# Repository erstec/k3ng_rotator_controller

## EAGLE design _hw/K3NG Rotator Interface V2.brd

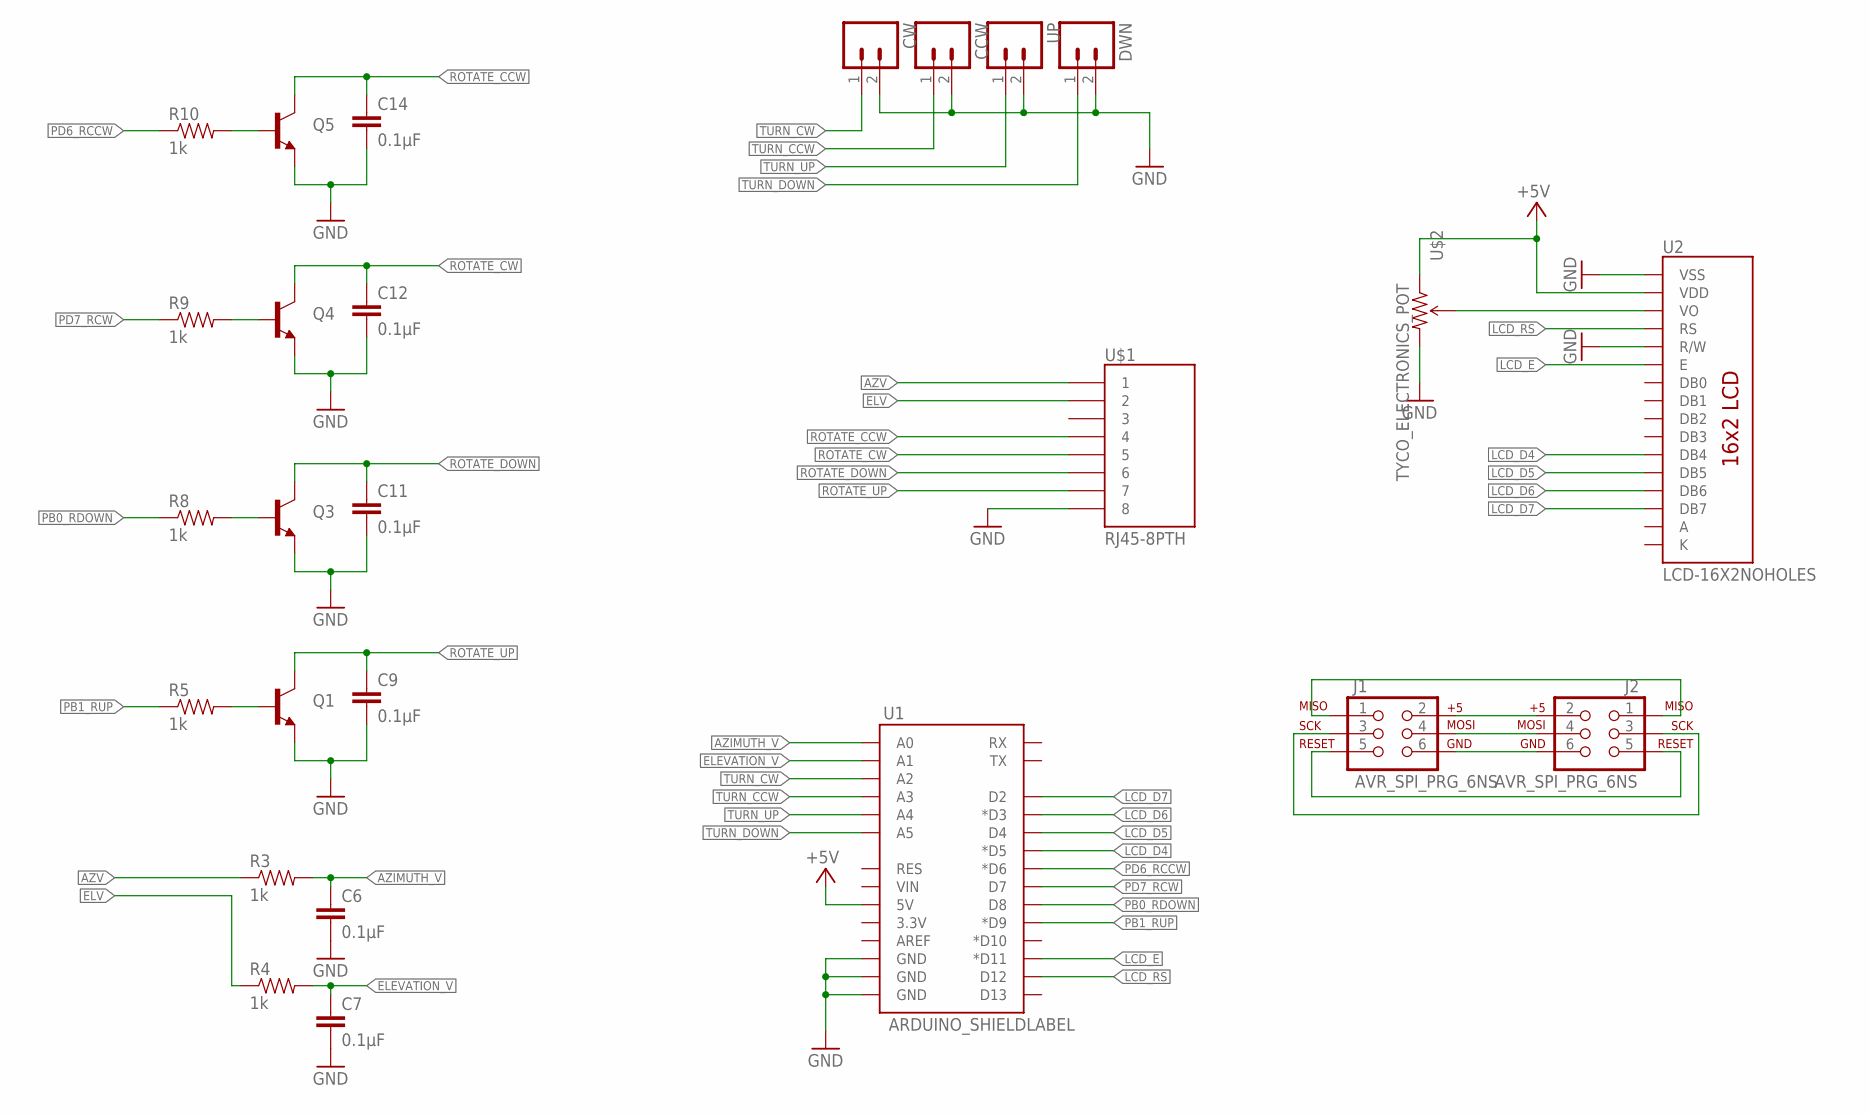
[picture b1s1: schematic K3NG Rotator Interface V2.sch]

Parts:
C6, C7, C9, C11, C12, C14: 0.1µF; 0603-CAP
CCW: M02PTH; 1X02
CW: M02PTH; 1X02
DWN: M02PTH; 1X02
J1, J2: AVR_SPI_PRG_6NS; 2X3-NS
Q1, Q3, Q4, Q5: TRANSISTOR_NPNSOT23; SOT23
R3, R4, R5, R8, R9, R10: 1k; 0805
U1: ARDUINO_SHIELDLABEL; DUEMILANOVE_SHIELD
U2: LCD-16X2NOHOLES; LCD-16X2_NOHOLES
U$1: RJ45-8PTH; RJ45-8
U$2: TYCO_ELECTRONICS_POT
UP: M02PTH; 1X02

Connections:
+5V: U1.5V, U2.2 (VDD), U$2.P$1 (CCW)
A: U2.15 (A)
AZIMUTH_V: C6.1, R3.2, U1.A0
AZV: R3.1, U$1.1
ELEVATION_V: C7.1, R4.2, U1.A1
ELV: R4.1, U$1.2
GND: C6.2, C7.2, C9.2, C11.2, C12.2, C14.2, CCW.2, CW.2, DWN.2, Q1.2 (E), Q3.2 (E), Q4.2 (E), Q5.2 (E), U1.GND@0 (GND), U1.GND@1 (GND), U1.GND@2 (GND), U2.1 (VSS), U2.5 (R/W), U$1.8, U$2.P$3 (CW), UP.2
K: U2.16 (K)
LCD_D4: U1.D5 (*D5), U2.11 (DB4)
LCD_D5: U1.D4, U2.12 (DB5)
LCD_D6: U1.D3 (*D3), U2.13 (DB6)
LCD_D7: U1.D2, U2.14 (DB7)
LCD_E: U1.D11 (*D11), U2.6 (E)
LCD_RS: U1.D12, U2.4 (RS)
unnamed: J1.2, J2.2
unnamed: J1.4, J2.4
unnamed: J1.6, J2.6
unnamed: J1.1, J2.1
unnamed: J1.5, J2.5
unnamed: J1.3, J2.3
unnamed: Q1.1 (B), R5.2
unnamed: Q3.1 (B), R8.2
unnamed: U2.3 (VO), U$2.P$2 (WIPER)
unnamed: Q4.1 (B), R9.2
unnamed: Q5.1 (B), R10.2
PB0_RDOWN: R8.1, U1.D8
PB1_RUP: R5.1, U1.D9 (*D9)
PD6_RCCW: R10.1, U1.D6 (*D6)
PD7_RCW: R9.1, U1.D7
ROTATE_CCW: C14.1, Q5.3 (C), U$1.4
ROTATE_CW: C12.1, Q4.3 (C), U$1.5
ROTATE_DOWN: C11.1, Q3.3 (C), U$1.6
ROTATE_UP: C9.1, Q1.3 (C), U$1.7
TURN_CCW: CCW.1, U1.A3
TURN_CW: CW.1, U1.A2
TURN_DOWN: DWN.1, U1.A5
TURN_UP: U1.A4, UP.1

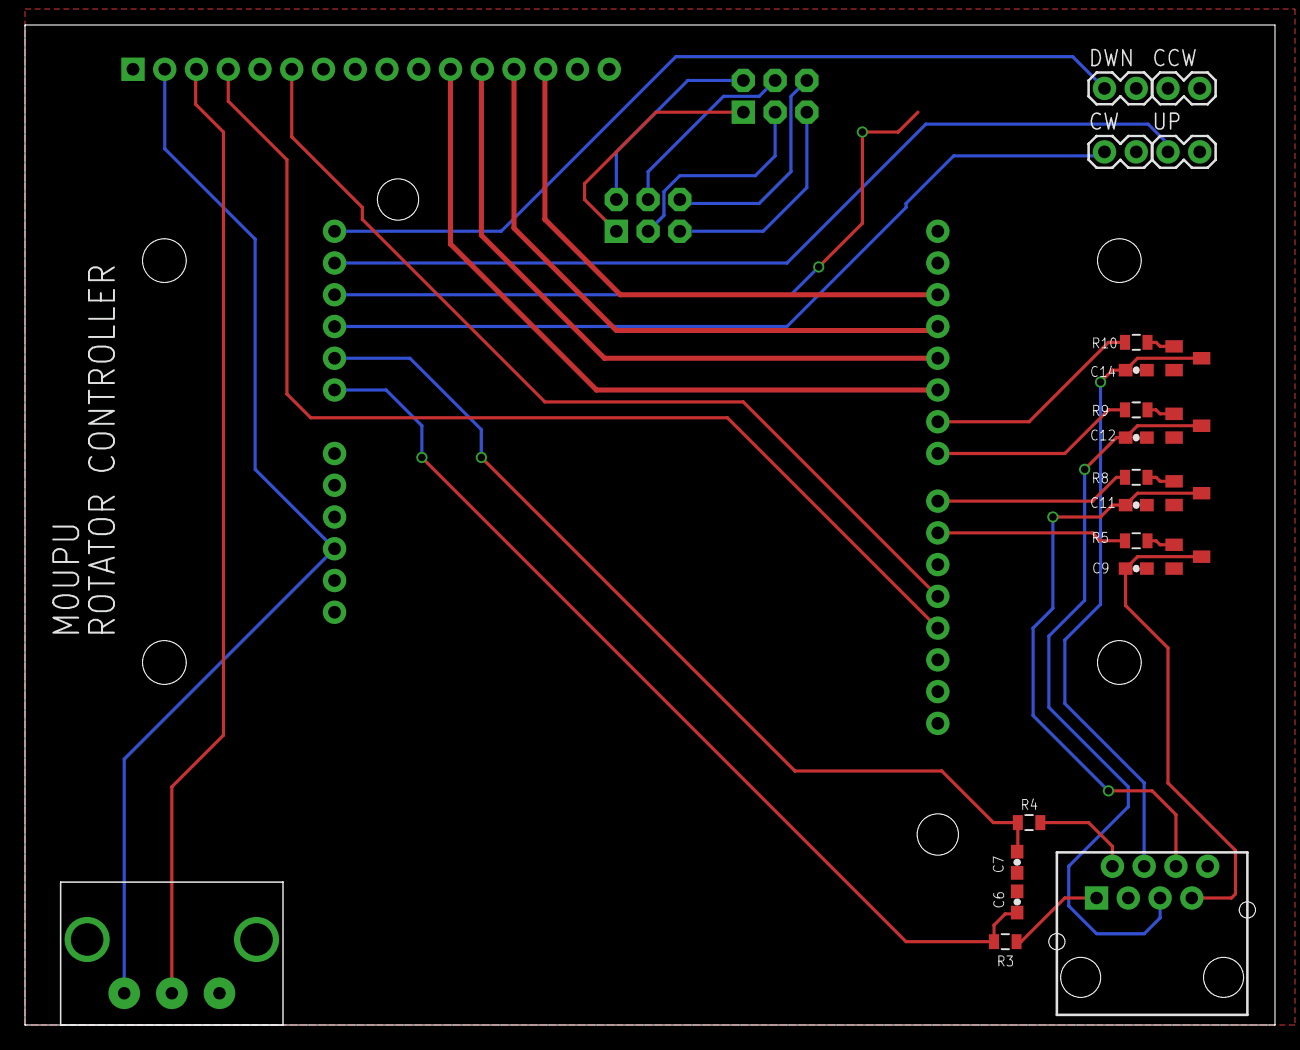
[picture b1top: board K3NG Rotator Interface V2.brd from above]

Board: 2 copper layers, 100.0 x 80.0 mm, 26 parts (1 on the bottom side), 35 nets.

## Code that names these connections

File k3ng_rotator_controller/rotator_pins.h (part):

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

#define pins_h
#define rotate_cw 7             // goes high to activate rotator R (CW) rotation - pin 1 on Yaesu connector  
#define rotate_ccw 6            // goes high to activate rotator L (CCW) rotation - pin 2 on Yaesu connector
#define rotate_cw_ccw  0         // goes high for both CW and CCW rotation
#define rotate_cw_pwm 0          // optional - PWM CW output - set to 0 to disable (must be PWM capable pin)
#define rotate_ccw_pwm 0         // optional - PWM CCW output - set to 0 to disable (must be PWM capable pin)
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// elevation pins
#ifdef FEATURE_ELEVATION_CONTROL
#define elevation_speed_voltage  0 // optional - PWM output for speed control voltage feed into rotator (on continually unlike rotate_up_pwm and rotate_down_pwm)
#define rotate_up 9//9               // goes high to activate rotator elevation up
#define rotate_down  8             // goes high to activate rotator elevation down
#define rotate_up_or_down 0
#define rotate_up_pwm 0          
#define rotate_down_pwm 0         
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
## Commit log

2023-08-18 HW mod
2023-09-09 configuration of board applied
2023-09-09 more corrections
2023-09-09 brake post-delay 3000->500
2023-09-22 Schematics, PCB and STLs added
2023-09-23 Default center - North (0 deg)
    Azimuth tolerance 1.0
2023-10-23 elevation control disable

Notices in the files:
parts and their libraries:
SparkFun: Licensing: CC v3.0 Share-Alike You are welcome to use this library for commercial purposes.
